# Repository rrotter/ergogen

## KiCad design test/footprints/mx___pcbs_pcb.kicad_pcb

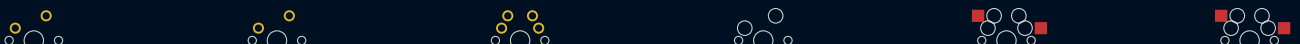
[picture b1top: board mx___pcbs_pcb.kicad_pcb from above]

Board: 2 copper layers, 6 parts (0 on the bottom side), 2 nets, no tracks yet.

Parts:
S1, S2, S3, S4, S5, S6: MX

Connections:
from: S1.1, S2.1, S3.1, S4.1, S5.1, S6.1
to: S1.2, S2.2, S3.2, S4.2, S5.2, S6.2

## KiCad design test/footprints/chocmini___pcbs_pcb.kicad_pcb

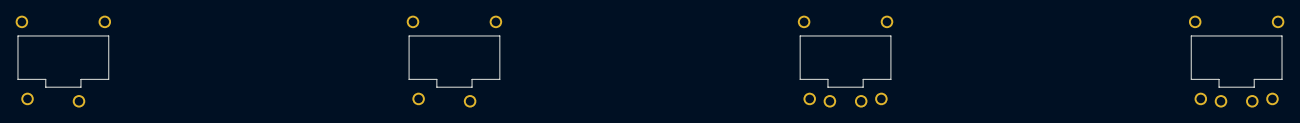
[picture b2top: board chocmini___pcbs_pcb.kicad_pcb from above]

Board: 2 copper layers, 4 parts (0 on the bottom side), 2 nets, no tracks yet.

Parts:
S1, S2, S3, S4: Kailh_PG1232

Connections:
from: S1.1, S2.1, S3.1, S4.1
to: S1.2, S2.2, S3.2, S4.2

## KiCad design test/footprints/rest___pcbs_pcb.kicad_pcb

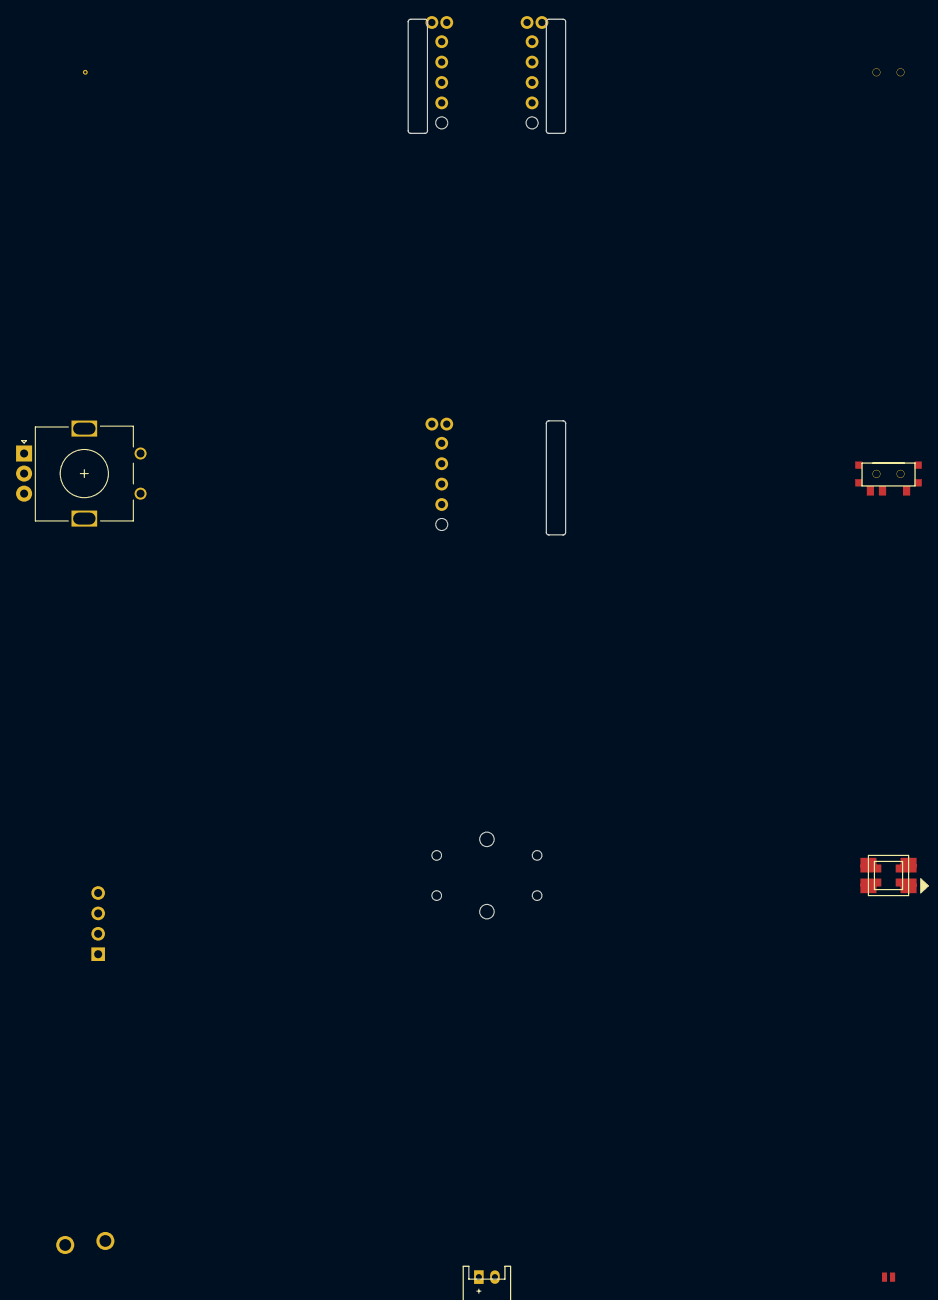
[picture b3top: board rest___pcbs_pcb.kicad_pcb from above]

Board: 2 copper layers, 9 parts (0 on the bottom side), 6 nets, no tracks yet.

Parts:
J1: Jumper
JST1: JST_PH_S2B-PH-K_02x2.00mm_Angled
LED1: WS2812B
OLED1: OLED; OLED_headers
ROT1: rotary_encoder
S1: ALPS
S2: OMRON_B3F-4055
T1, T2: SPDT_C128955

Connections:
GND: LED1.3, LED1.33, OLED1.1
VCC: LED1.1, LED1.11, OLED1.2
din: LED1.4, LED1.44
dout: LED1.2, LED1.22
from: J1.1, ROT1.1, S1.1, S2.1, S2.2, T1.1, T2.1
to: J1.2, ROT1.2, S1.2, S2.3, S2.4, T1.2, T2.2

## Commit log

2023-05-29 New Kicad format plus tests
2023-05-29 Add parenthesis to title block
2023-05-30 clean up pcb output formatting, upgrade to kicad 7
    - consistant indenting (where possible without editing footprint libraries)
    - setup block matches a new file generated in KiCad 7.0.2
    - changed generator string in header, per https://dev-docs.kicad.org/en/file-formats/sexpr-pcb/#_header_section
    - delete default net class
    - pad_to_mask_clearance 0
